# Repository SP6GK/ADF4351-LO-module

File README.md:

# High Quality RF Local Oscillator Module (ADF4351)

## Overview

This open-source PCB module is designed as a **drop in solution** for any project that requires a **high quality RF continuous wave signal** with at least **16 dBm output power**.  

I present more details on my website: [www.sp6gk.com](https://www.sp6gk.com/).

The design emphasizes:

- Output power (16–20 dBm depending on frequency)
- Low phase noise
- Minimal harmonics
- Easy integration into custom designs

Originally developed for the **Presto HF to QO-100 transverter project**, this module can be used in a wide variety of RF applications.

---

## Features & Specifications

| Parameter | Value |
|-----------|-------|
| **Optimal Frequency Range** | 400 MHz – 800 MHz (tunable for other ranges) or 1.5-2.1 GHz |
| **Output Power** | 20 dBm (50 Ω load) within optimal range |
| **Power Across Wide Range** | >17 dBm from 100 MHz to 2.4 GHz |
| **Phase Noise @ 400 MHz CW** | -89 dBc/Hz @ 100 Hz offset<br>-97 dBc/Hz @ 10 kHz offset |
| **Reference** | onboard 48 MHz 0.5 ppm VCTCXO + 12-bit DAC digital tuning (or external reference) |
| **Filtering** | Two selectable low-pass filters |
| **PLL Chipset** | Fractional-N PLL (Analog Devices ADF4351) |
| **Dimensions** | 85 × 57 mm |
| **Supply Voltage** | 3.6 V recommended (5.5 V absolute maximum) for logic, 5.3 V for PA stage (5.5 V absolute maximum) |
| **Current Consumption** | < 250 mA (can be reduced by disabling output) |
| **Calibration Storage** | On-board EEPROM |
| **Interface** | SPI (programming PLL) + 3.3 V input pins for switching filters, PA enable etc... |

---

## Applications

- Test and Measurement Equipment
- VHF/UHF Communication Systems
- Amateur Radio
- Backhaul network

---

## Current revisions:
- 400 to 800 MHz rev 01a (tested and presented in the measurements)
- 400 to 800 MHz rev 01b (adds triplexer before amplifier to minimize reflections)
- 1.5-2.1 GHz rev 01a (tuned for higher frequency, includes triplexer and microstrip LPF)

## Performance Measurements

Testing was performed using a **Keysight CXA Spectrum Analyzer (N9000B)** with the **phase noise measurement** option.

**100 MHz**  

**400 MHz**  

**1.2 GHz**  

---

### Harmonics & Output Spectra

**100 MHz CW (50 MHz span)**  

**400 MHz CW (10 MHz span)**  

---
Module was tested with STM32F407 discovery board, using driver written by [KB3GTN](https://github.com/kb3gtn/STM32_ADF4351).

---
### What's next?

I intended to use this module for driving a passive RF mixer, however since then I have learned that those work better with square wave LO with lower amplitude.

Currently I am working on revision of this board with LMX2572LP.
I have found this IC to be easier to program while offering better performance especially in terms of spurious emissions.

---

## Repository Contents
- **/ECAD** (Kicad Project, simulations)
- **/Fabrication** (Gerbers)
- **/Verification** (Measurements)
- **/Documents** (BOM)
- **/Photos** (photos of assembled PCB)

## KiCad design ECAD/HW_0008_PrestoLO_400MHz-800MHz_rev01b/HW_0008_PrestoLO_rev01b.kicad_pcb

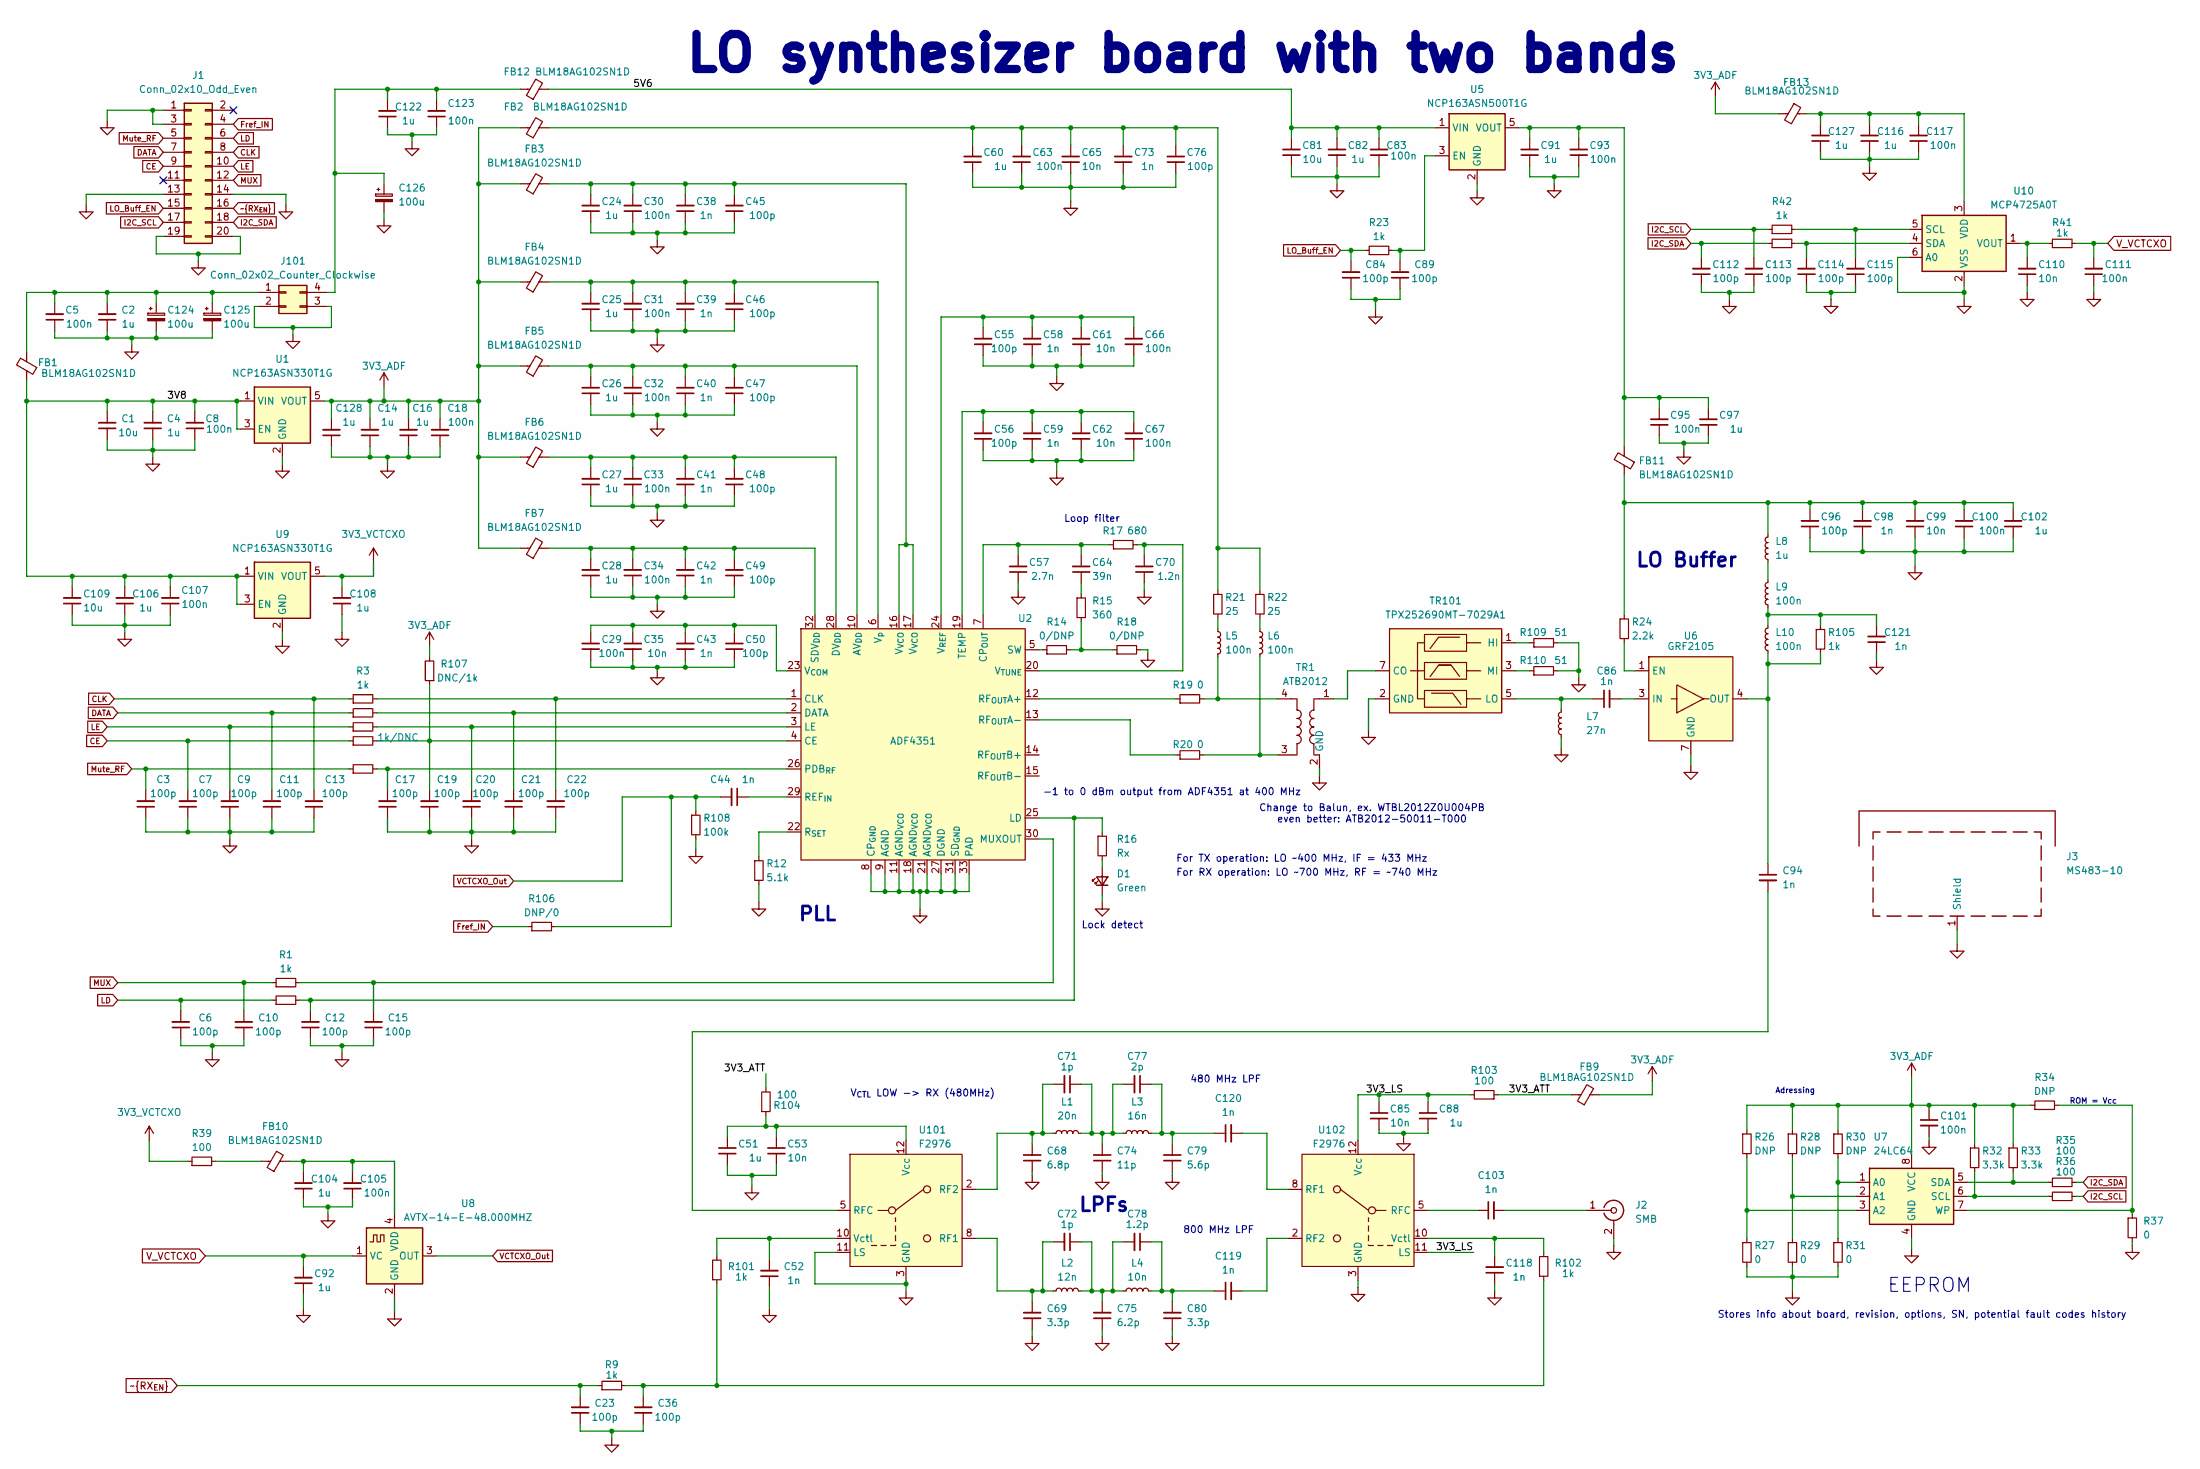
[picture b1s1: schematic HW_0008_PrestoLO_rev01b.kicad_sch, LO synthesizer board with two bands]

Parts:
C1, C81, C109: 10u; LED_0805_2012Metric
C2, C82, C91, C97, C122: 1u; C_0805_2012Metric_Pad1.18x1.45mm_HandSolder
C3, C6, C7, C9, C10, C11, C12, C13, C15, C17, C19, C20, C21, C22, C23, C36, C45, C46, C47, C48, C49, C50, C55, C56, C76, C84, C89, C96, C112, C113, C114, C115: 100p; C_0603_1608Metric_Pad1.08x0.95mm_HandSolder
C4, C14, C16, C24, C25, C26, C27, C28, C51, C60, C88, C92, C102, C104, C106, C108, C116, C127, C128: 1u; C_0603_1608Metric_Pad1.08x0.95mm_HandSolder
C5, C8, C18, C29, C30, C31, C32, C33, C34, C63, C66, C67, C83, C93, C95, C100, C101, C105, C107, C111, C117: 100n; C_0603_1608Metric_Pad1.08x0.95mm_HandSolder
C35, C61, C62, C65, C99, C110: 10n; C_0603_1608Metric_Pad1.08x0.95mm_HandSolder
C38, C39, C40, C41, C42, C43, C44, C58, C59, C73, C86, C94, C98, C103, C119, C120, C121: 1n; C_0603_1608Metric_Pad1.08x0.95mm_HandSolder
C52, C118: 1n; C_0402_1005Metric_Pad0.74x0.62mm_HandSolder
C53, C85: 10n; C_0402_1005Metric_Pad0.74x0.62mm_HandSolder
C57: 2.7n; C_0603_1608Metric_Pad1.08x0.95mm_HandSolder
C64: 39n; C_0603_1608Metric_Pad1.08x0.95mm_HandSolder
C68: 6.8p; C_0603_1608Metric
C69, C80: 3.3p; C_0603_1608Metric
C70: 1.2n; C_0603_1608Metric_Pad1.08x0.95mm_HandSolder
C71, C72: 1p; C_0603_1608Metric
C74: 11p; C_0603_1608Metric
C75: 6.2p; C_0603_1608Metric
C77: 2p; C_0603_1608Metric
C78: 1.2p; C_0603_1608Metric
C79: 5.6p; C_0603_1608Metric
C123: 100n; C_0805_2012Metric_Pad1.18x1.45mm_HandSolder
C124, C125, C126: 100u; CP_Elec_6.3x5.8
D1: Green; D_0805_2012Metric_Pad1.15x1.40mm_HandSolder
FB1: BLM18AG102SN1D; L_0805_2012Metric_Pad1.15x1.40mm_HandSolder
FB2, FB3, FB4, FB5, FB6, FB7, FB9, FB10, FB11, FB13: BLM18AG102SN1D; L_0603_1608Metric_Pad1.05x0.95mm_HandSolder
FB12: BLM18AG102SN1D; L_0805_2012Metric_Pad1.05x1.20mm_HandSolder
J1: Conn_02x10_Odd_Even; PinHeader_2x10_P2.54mm_Vertical
J2: SMB; SMB_Jack_Vertical
J3: MS483-10; MS4830-10
J101: Conn_02x02_Counter_Clockwise; PinHeader_2x02_P2.54mm_Vertical
L1: 20n; L_0603_1608Metric
L2: 12n; L_0603_1608Metric
L3: 16n; L_0603_1608Metric
L4: 10n; L_0603_1608Metric
L5, L6: 100n; L_0805_2012Metric_Pad1.15x1.40mm_HandSolder
L7: 27n; L_0805_2012Metric_Pad1.05x1.20mm_HandSolder
L8: 1u; L_0805_2012Metric_Pad1.05x1.20mm_HandSolder
L9: 100n; L_0805_2012Metric_Pad1.05x1.20mm_HandSolder
L10: 100n; L_0603_1608Metric_Pad1.05x0.95mm_HandSolder
R1, R2, R3, R4, R5, R7, R9, R23, R41, R42, R43, R105: 1k; R_0603_1608Metric_Pad0.98x0.95mm_HandSolder
R6: 1k/DNC; R_0603_1608Metric_Pad0.98x0.95mm_HandSolder
R12: 5.1k; R_0603_1608Metric_Pad0.98x0.95mm_HandSolder
R14, R18: 0/DNP; R_0603_1608Metric_Pad0.98x0.95mm_HandSolder
R15: 360; R_0603_1608Metric_Pad0.98x0.95mm_HandSolder
R16: Rx; R_0603_1608Metric_Pad0.98x0.95mm_HandSolder
R17: 680; R_0603_1608Metric_Pad0.98x0.95mm_HandSolder
R19, R20, R37: 0; R_0603_1608Metric_Pad0.98x0.95mm_HandSolder
R21, R22: 25; R_0603_1608Metric_Pad0.98x0.95mm_HandSolder
R24: 2.2k; R_0603_1608Metric_Pad0.98x0.95mm_HandSolder
R26, R28, R30: DNP; R_0805_2012Metric_Pad1.20x1.40mm_HandSolder
R27, R29, R31: 0; R_0805_2012Metric_Pad1.20x1.40mm_HandSolder
R32, R33: 3.3k; R_0603_1608Metric_Pad0.98x0.95mm_HandSolder
R34: DNP; R_0603_1608Metric_Pad0.98x0.95mm_HandSolder
R35, R36, R39: 100; R_0603_1608Metric_Pad0.98x0.95mm_HandSolder
R101, R102: 1k; R_0402_1005Metric_Pad0.72x0.64mm_HandSolder
R103, R104: 100; R_0402_1005Metric_Pad0.72x0.64mm_HandSolder
R106: DNP/0; R_0603_1608Metric_Pad0.98x0.95mm_HandSolder
R107: DNC/1k; R_0603_1608Metric_Pad0.98x0.95mm_HandSolder
R108: 100k; R_0603_1608Metric_Pad0.98x0.95mm_HandSolder
R109, R110: 51; R_0603_1608Metric_Pad0.98x0.95mm_HandSolder
TR1: ATB2012
TR101: TPX252690MT-7029A1; TPX252690MT-7029A
U1, U9: NCP163ASN330T1G; SOT-23-5
U2: ADF4351; LFCSP-32-1EP_5x5mm_P0.5mm_EP3.5x3.5mm_ThermalVias
U5: NCP163ASN500T1G; SOT-23-5
U6: GRF2105; DFN-6-1EP_2x2mm_P0.5mm_EP0.6x1.37mm
U7: 24LC64; SOIC-8_3.9x4.9mm_P1.27mm
U8: AVTX-14-E-48.000MHZ; AbracomAVTX_14
U10: MCP4725A0T; SOT-23-6
U101, U102: F2976

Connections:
3V3_ADF: C14.2, C16.2, C18.2, C101.1, C128.2, FB2.1, FB3.1, FB4.1, FB5.1, FB6.1, FB7.1, FB9.2, FB13.2, R26.1, R28.1, R30.1, R32.1, R33.1, R34.1, R107.2, U1.5 (VOUT), U7.8 (VCC)
3V3_VCTCXO: C108.2, R39.1, U9.5 (VOUT)
/3V3_ATT: FB9.1, R103.1, R104.2
/3V3_LS: C85.2, C88.2, R103.2, U102.11 (LS), U102.12 (Vcc)
/3V8: C1.2, C4.2, C8.2, C106.2, C107.2, C109.2, FB1.1, U1.1 (VIN), U1.3 (EN), U9.1 (VIN), U9.3 (EN)
/5V6: C81.2, C82.2, C83.2, FB12.2, U5.1 (VIN)
CE: C7.2, J1.9, R6.1
CLK: C13.2, J1.8, R3.1
DATA: C11.2, J1.7, R4.1
Fref_IN: J1.4, R106.1
GND: C1.1, C2.1, C3.1, C4.1, C5.1, C6.1, C7.1, C8.1, C9.1, C10.1, C11.1, C12.1, C13.1, C14.1, C15.1, C16.1, C17.1, C18.1, C19.1, C20.1, C21.1, C22.1, C23.1, C24.1, C25.1, C26.1, C27.1, C28.1, C29.1, C30.1, C31.1, C32.1, C33.1, C34.1, C35.1, C36.1, C38.1, C39.1, C40.1, C41.1, C42.1, C43.1, C45.1, C46.1, C47.1, C48.1, C49.1, C50.1, C51.1, C52.1, C53.1, C55.1, C56.1, C57.1, C58.1, C59.1, C60.1, C61.1, C62.1, C63.1, C65.1, C66.1, C67.1, C68.1, C69.1, C70.1, C73.1, C74.1, C75.1, C76.1, C79.1, C80.1, C81.1, C82.1, C83.1, C84.1, C85.1, C88.1, C89.1, C91.1, C92.1, C93.1, C95.1, C96.1, C97.1, C98.1, C99.1, C100.1, C101.2, C102.1, C104.1, C105.1, C106.1, C107.1, C108.1, C109.1, C110.1, C111.1, C112.1, C113.1, C114.1, C115.1, C116.1, C117.1, C118.1, C121.1, C122.1, C123.1, C124.2, C125.2, C126.2, C127.1, C128.1, D1.1 (K), J1.1, J1.3, J1.13, J1.14, J1.19, J1.20, J2.2 (Ext), J3.1 (Shield), J101.2, J101.3, L7.1, R12.2, R18.2, R27.2, R29.2, R31.2, R37.2, R108.2, R109.2, R110.2, TR1.2 (GND), TR101.2 (GND), TR101.4 (GND), TR101.6 (GND), TR101.8 (GND), TR101.9 (GND), U1.2 (GND), U2.8 (CP_{GND}), U2.9 (AGND), U2.11 (AGND_{VCO}), U2.18 (AGND_{VCO}), U2.21 (AGND_{VCO}), U2.27 (DGND), U2.31 (SD_{GND}), U2.33 (PAD), U5.2 (GND), U6.2 (GND), U6.5 (GND), U6.6 (GND), U6.7 (GND), U7.4 (GND), U8.2 (GND), U9.2 (GND), U10.2 (VSS), U10.6 (A0), U101.1 (GND), U101.3 (GND), U101.4 (GND), U101.6 (GND), U101.7 (GND), U101.9 (GND), U101.11 (LS), U101.EP (GND), U102.1 (GND), U102.3 (GND), U102.4 (GND), U102.6 (GND), U102.7 (GND), U102.9 (GND), U102.EP (GND)
I2C_SCL: C113.2, J1.17, R36.2, R42.1
I2C_SDA: C112.2, J1.18, R35.2, R43.1
LD: C6.2, J1.6, R2.1
LE: C9.2, J1.10, R5.1
LO_Buff_EN: C84.2, J1.15, R23.1
MUX: C10.2, J1.12, R1.1
Mute_RF: C3.2, J1.5, R7.1
unnamed: C24.2, C30.2, C38.2, C45.2, FB3.2, U2.16 (V_{VCO}), U2.17 (V_{VCO})
unnamed: C36.2, R9.2, R101.1, R102.1
unnamed: C60.2, C63.2, C65.2, C73.2, C76.2, FB2.2, R21.1, R22.1
unnamed: C64.1, R15.1
unnamed: C71.1, C74.2, C77.2, L1.2, L3.1
unnamed: C72.1, C75.2, C78.2, L2.2, L4.1
unnamed: C96.2, C98.2, C99.2, C100.2, C102.2, FB11.1, L8.2, R24.1
unnamed: C78.1, C80.2, C119.1, L4.2
unnamed: C77.1, C79.2, C120.1, L3.2
unnamed: C121.2, L9.1, L10.2, R105.1
unnamed: D1.2 (A), R16.2
unnamed: FB10.1, R39.2
unnamed: C103.2, J2.1 (In)
unnamed: C2.2, C5.2, C124.1, C125.1, FB1.2, J101.1
unnamed: C122.2, C123.2, C126.1, FB12.1, J101.4
unnamed: L5.1, R21.2
unnamed: L5.2, R19.2, TR1.4
unnamed: L6.1, R22.2
unnamed: L6.2, R20.2, TR1.3
unnamed: L8.1, L9.2
unnamed: R14.2, R15.2, R18.1
unnamed: TR1.1, TR101.7 (CO)
unnamed: R109.1, TR101.1 (HI)
unnamed: C86.1, L7.2, TR101.5 (LO)
unnamed: R110.1, TR101.3 (MI)
unnamed: C26.2, C32.2, C40.2, C47.2, FB5.2, U2.10 (AV_{DD})
unnamed: C19.2, R6.2, R107.1, U2.4 (CE)
unnamed: C22.2, R3.2, U2.1 (CLK)
unnamed: C57.2, C64.2, R17.1, U2.7 (CP_{OUT})
unnamed: C21.2, R4.2, U2.2 (DATA)
unnamed: C27.2, C33.2, C41.2, C48.2, FB6.2, U2.28 (DV_{DD})
unnamed: C12.2, R2.2, R16.1, U2.25 (LD)
unnamed: C20.2, R5.2, U2.3 (LE)
unnamed: C15.2, R1.2, U2.30 (MUXOUT)
unnamed: C17.2, R7.2, U2.26 (PDB_{RF})
unnamed: C44.1, U2.29 (REF_{IN})
unnamed: R19.1, U2.12 (RF_{OUT}A+)
unnamed: R20.1, U2.13 (RF_{OUT}A-)
unnamed: R12.1, U2.22 (R_{SET})
unnamed: C28.2, C34.2, C42.2, C49.2, FB7.2, U2.32 (SDV_{DD})
unnamed: R14.1, U2.5 (SW)
unnamed: C56.2, C59.2, C62.2, C67.2, U2.19 (TEMP)
unnamed: C29.2, C35.2, C43.2, C50.2, U2.23 (V_{COM})
unnamed: C55.2, C58.2, C61.2, C66.2, U2.24 (V_{REF})
unnamed: C70.2, R17.2, U2.20 (V_{TUNE})
unnamed: C25.2, C31.2, C39.2, C46.2, FB4.2, U2.6 (V_{p})
unnamed: C89.2, R23.2, U5.3 (EN)
unnamed: C91.2, C93.2, C95.2, C97.2, FB11.2, U5.5 (VOUT)
unnamed: R24.2, U6.1 (EN)
unnamed: C86.2, U6.3 (IN)
unnamed: C94.1, L10.1, R105.2, U6.4 (OUT)
unnamed: R30.2, R31.1, U7.1 (A0)
unnamed: R28.2, R29.1, U7.2 (A1)
unnamed: R26.2, R27.1, U7.3 (A2)
unnamed: R32.2, R36.1, U7.6 (SCL)
unnamed: R33.2, R35.1, U7.5 (SDA)
unnamed: R34.2, R37.1, U7.7 (WP)
unnamed: C104.2, C105.2, FB10.2, U8.4 (VDD)
unnamed: C115.2, R42.2, U10.5 (SCL)
unnamed: C114.2, R43.2, U10.4 (SDA)
unnamed: C116.2, C117.2, C127.2, FB13.1, U10.3 (VDD)
unnamed: C110.2, R41.1, U10.1 (VOUT)
unnamed: C69.2, C72.2, L2.1, U101.8 (RF1)
unnamed: C68.2, C71.2, L1.1, U101.2 (RF2)
unnamed: C94.2, U101.5 (RFC)
unnamed: C51.2, C53.2, R104.1, U101.12 (Vcc)
unnamed: C52.2, R101.2, U101.10 (Vctl)
unnamed: C120.2, U102.8 (RF1)
unnamed: C119.2, U102.2 (RF2)
unnamed: C103.1, U102.5 (RFC)
unnamed: C118.2, R102.2, U102.10 (Vctl)
VCTCXO_Out: C44.2, R106.2, R108.1, U8.3 (OUT)
V_VCTCXO: C92.2, C111.2, R41.2, U8.1 (VC)
~RX_{EN}: C23.2, J1.16, R9.1

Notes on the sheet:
EEPROM
LPFs
Adressing
-1 to 0 dBm output from ADF4351 at 400 MHz
800 MHz LPF
480 MHz LPF
Lock detect
PLL
For TX operation: LO ~400 MHz, IF = 433 MHz
LO Buffer
Loop filter
LO synthesizer board with two bands
For RX operation: LO ~700 MHz, RF = ~740 MHz
Stores info about board, revision, options, SN, potential fault codes history
Change to Balun, ex. WTBL2012Z0U004PB even better: ATB2012-50011-T000
ROM = Vcc
V_{CTL} LOW -> RX (480MHz)

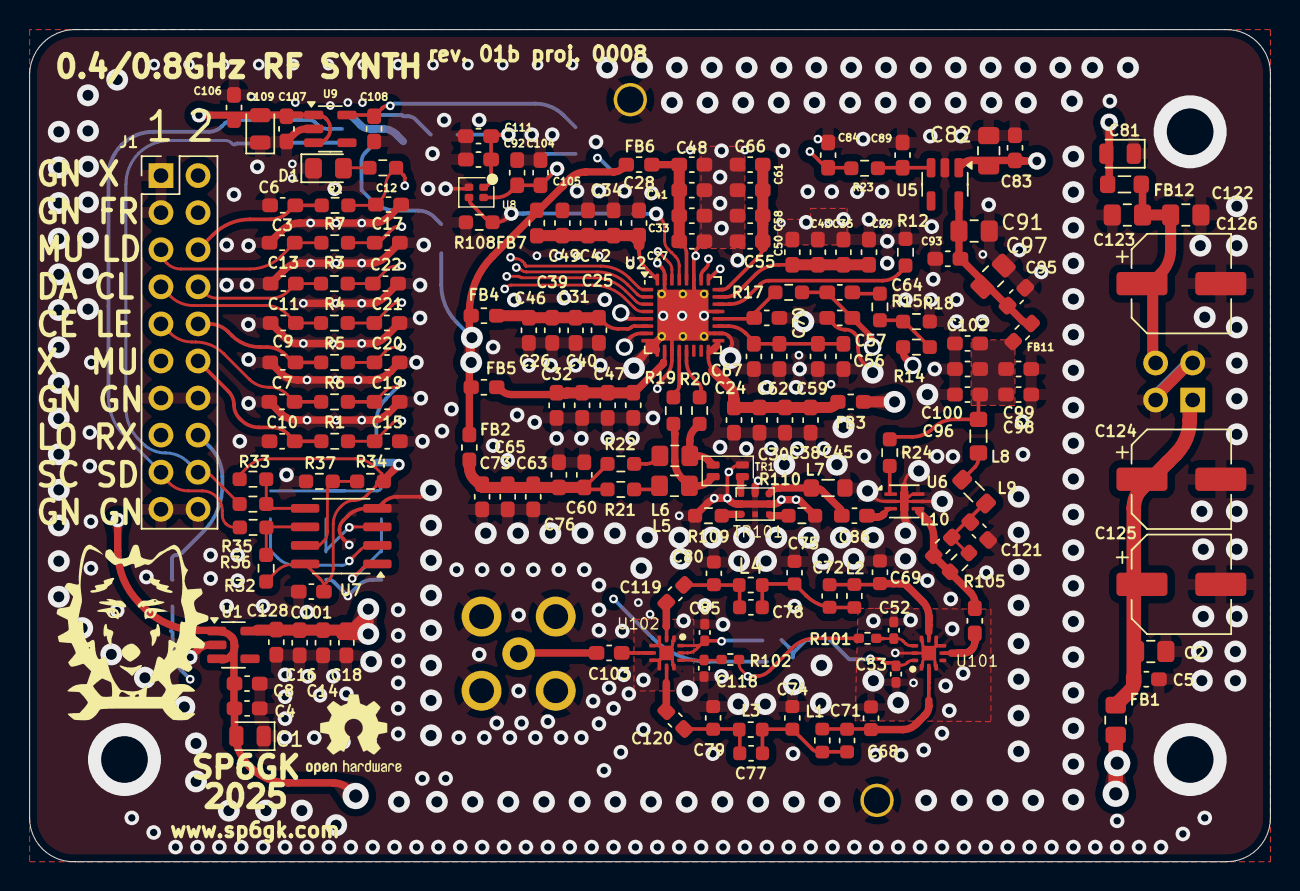
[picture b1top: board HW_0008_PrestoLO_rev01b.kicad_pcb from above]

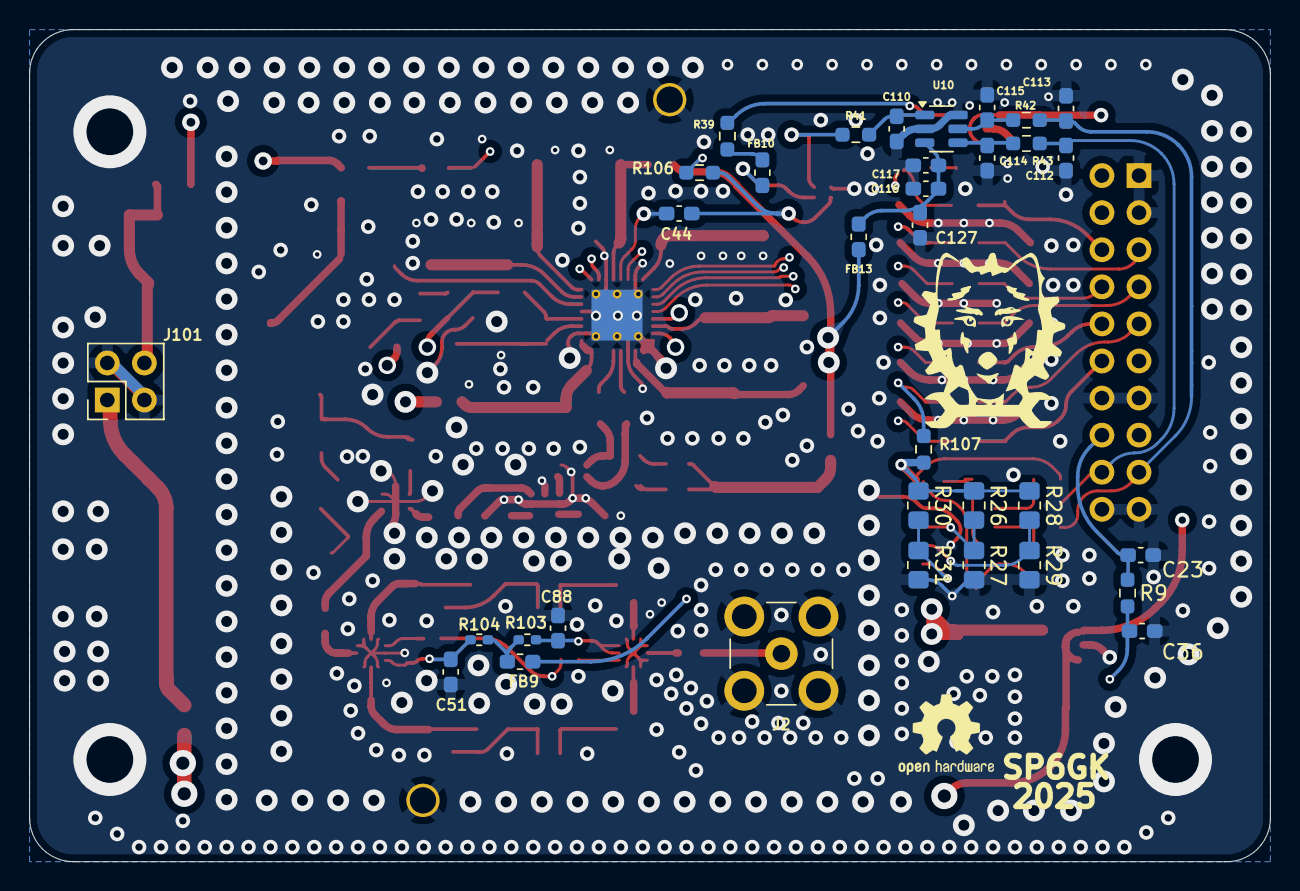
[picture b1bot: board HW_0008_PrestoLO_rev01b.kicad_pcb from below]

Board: 4 copper layers, 85.0 x 57.0 mm, 209 parts (34 on the bottom side), 92 nets.

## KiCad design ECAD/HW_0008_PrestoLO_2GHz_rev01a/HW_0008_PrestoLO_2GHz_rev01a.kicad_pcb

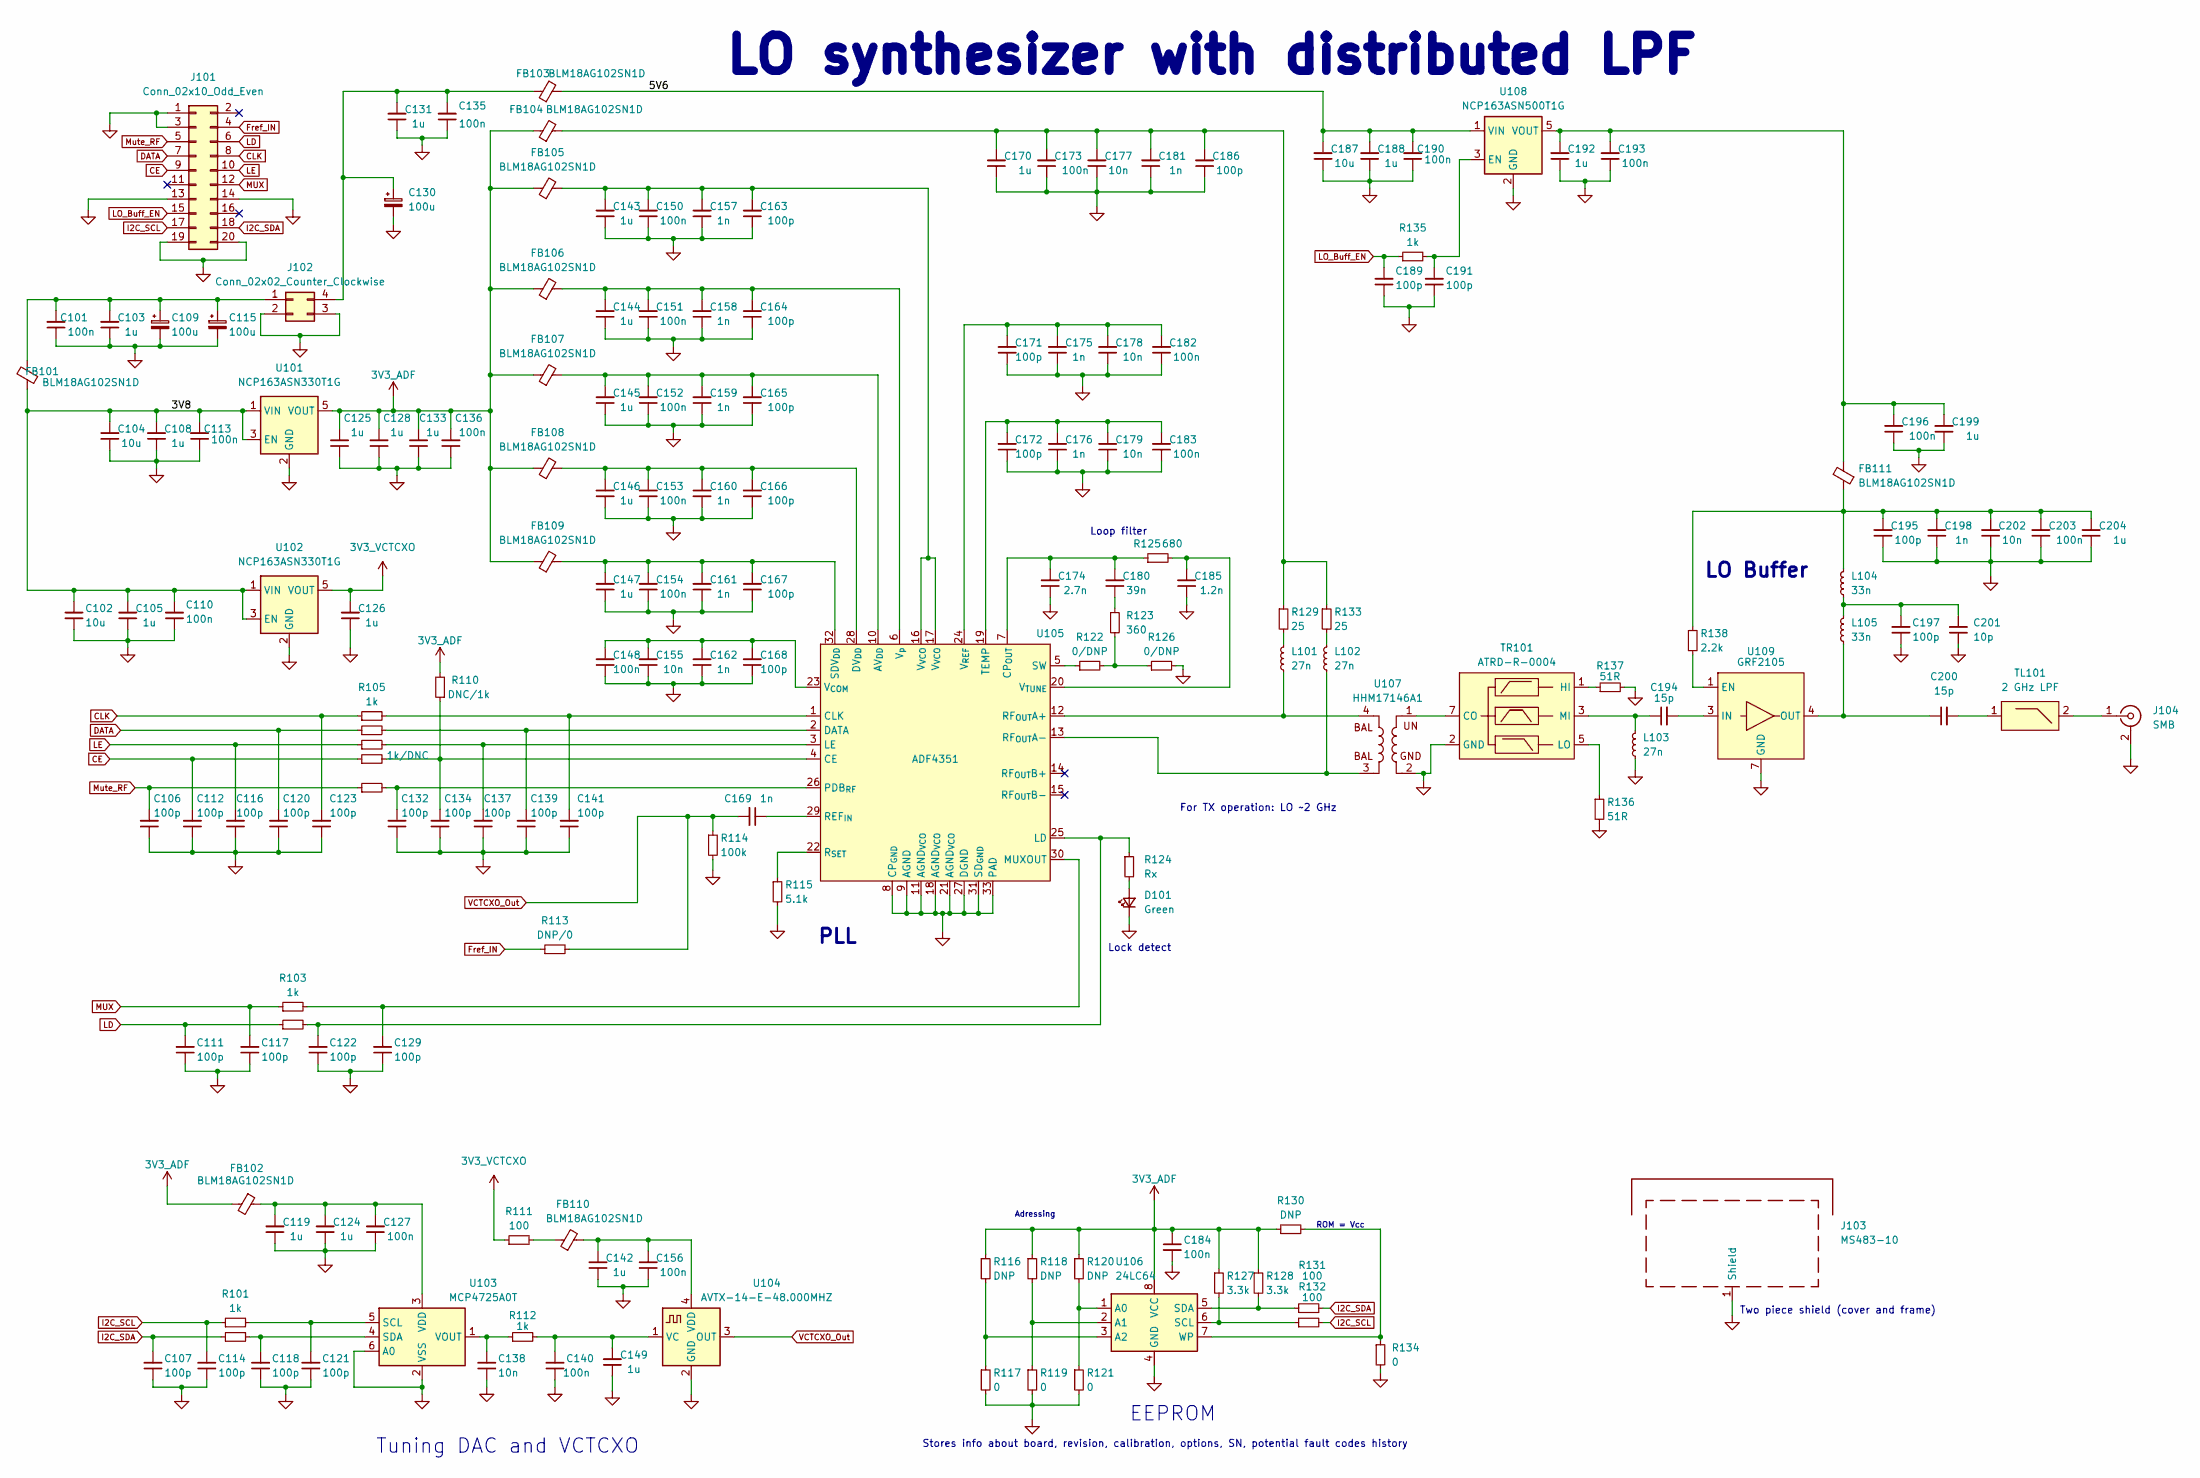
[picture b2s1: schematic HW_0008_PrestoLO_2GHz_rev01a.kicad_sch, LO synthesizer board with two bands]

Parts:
C101, C110, C113, C127, C136, C140, C148, C150, C151, C152, C153, C154, C156, C173, C182, C183, C184, C190, C193, C196, C203: 100n; C_0603_1608Metric_Pad1.08x0.95mm_HandSolder
C102, C104, C187: 10u; LED_0805_2012Metric
C103, C131, C188, C192, C199: 1u; C_0805_2012Metric_Pad1.18x1.45mm_HandSolder
C105, C108, C119, C124, C125, C126, C128, C133, C142, C143, C144, C145, C146, C147, C149, C170, C204: 1u; C_0603_1608Metric_Pad1.08x0.95mm_HandSolder
C106, C107, C111, C112, C114, C116, C117, C118, C120, C121, C122, C123, C129, C132, C134, C137, C139, C141, C163, C164, C165, C166, C167, C168, C171, C172, C186, C189, C191, C195, C197: 100p; C_0603_1608Metric_Pad1.08x0.95mm_HandSolder
C109, C115, C130: 100u; CP_Elec_6.3x5.8
C135: 100n; C_0805_2012Metric_Pad1.18x1.45mm_HandSolder
C138, C155, C177, C178, C179, C202: 10n; C_0603_1608Metric_Pad1.08x0.95mm_HandSolder
C157, C158, C159, C160, C161, C162, C169, C175, C176, C181, C198: 1n; C_0603_1608Metric_Pad1.08x0.95mm_HandSolder
C174: 2.7n; C_0603_1608Metric_Pad1.08x0.95mm_HandSolder
C180: 39n; C_0603_1608Metric_Pad1.08x0.95mm_HandSolder
C185: 1.2n; C_0603_1608Metric_Pad1.08x0.95mm_HandSolder
C194, C200: 15p; C_0603_1608Metric_Pad1.08x0.95mm_HandSolder
C201: 10p; C_0603_1608Metric_Pad1.08x0.95mm_HandSolder
D101: Green; D_0805_2012Metric_Pad1.15x1.40mm_HandSolder
FB101: BLM18AG102SN1D; L_0805_2012Metric_Pad1.15x1.40mm_HandSolder
FB102, FB104, FB105, FB106, FB107, FB108, FB109, FB110, FB111: BLM18AG102SN1D; L_0603_1608Metric_Pad1.05x0.95mm_HandSolder
FB103: BLM18AG102SN1D; L_0805_2012Metric_Pad1.05x1.20mm_HandSolder
J101: Conn_02x10_Odd_Even; PinHeader_2x10_P2.54mm_Vertical
J102: Conn_02x02_Counter_Clockwise; PinHeader_2x02_P2.54mm_Vertical
J103: MS483-10; MS4830-10
J104: SMB; SMB_Jack_Vertical
L101, L102, L103: 27n; L_0805_2012Metric_Pad1.05x1.20mm_HandSolder
L104, L105: 33n; L_0603_1608Metric_Pad1.05x0.95mm_HandSolder
R101, R102, R103, R104, R105, R106, R107, R109, R112, R135: 1k; R_0603_1608Metric_Pad0.98x0.95mm_HandSolder
R108: 1k/DNC; R_0603_1608Metric_Pad0.98x0.95mm_HandSolder
R110: DNC/1k; R_0603_1608Metric_Pad0.98x0.95mm_HandSolder
R111, R131, R132: 100; R_0603_1608Metric_Pad0.98x0.95mm_HandSolder
R113: DNP/0; R_0603_1608Metric_Pad0.98x0.95mm_HandSolder
R114: 100k; R_0603_1608Metric_Pad0.98x0.95mm_HandSolder
R115: 5.1k; R_0603_1608Metric_Pad0.98x0.95mm_HandSolder
R116, R118, R120: DNP; R_0805_2012Metric_Pad1.20x1.40mm_HandSolder
R117, R119, R121: 0; R_0805_2012Metric_Pad1.20x1.40mm_HandSolder
R122, R126: 0/DNP; R_0603_1608Metric_Pad0.98x0.95mm_HandSolder
R123: 360; R_0603_1608Metric_Pad0.98x0.95mm_HandSolder
R124: Rx; R_0603_1608Metric_Pad0.98x0.95mm_HandSolder
R125: 680; R_0603_1608Metric_Pad0.98x0.95mm_HandSolder
R127, R128: 3.3k; R_0603_1608Metric_Pad0.98x0.95mm_HandSolder
R129, R133: 25; R_0603_1608Metric_Pad0.98x0.95mm_HandSolder
R130: DNP; R_0603_1608Metric_Pad0.98x0.95mm_HandSolder
R134: 0; R_0603_1608Metric_Pad0.98x0.95mm_HandSolder
R136, R137: 51R; R_0402_1005Metric_Pad0.72x0.64mm_HandSolder
R138: 2.2k; R_0603_1608Metric_Pad0.98x0.95mm_HandSolder
TL101: 2 GHz LPF; Microstrip_2GHz_LPF
TR101: ATRD-R-0004; TPX252690MT-7029A
U101, U102: NCP163ASN330T1G; SOT-23-5
U103: MCP4725A0T; SOT-23-6
U104: AVTX-14-E-48.000MHZ; AbracomAVTX_14
U105: ADF4351; LFCSP-32-1EP_5x5mm_P0.5mm_EP3.5x3.5mm_ThermalVias
U106: 24LC64; SOIC-8_3.9x4.9mm_P1.27mm
U107: HHM17146A1
U108: NCP163ASN500T1G; SOT-23-5
U109: GRF2105; DFN-6-1EP_2x2mm_P0.5mm_EP0.6x1.37mm

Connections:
3V3_ADF: C125.2, C128.2, C133.2, C136.2, C184.1, FB102.2, FB104.1, FB105.1, FB106.1, FB107.1, FB108.1, FB109.1, R110.2, R116.1, R118.1, R120.1, R127.1, R128.1, R130.1, U101.5 (VOUT), U106.8 (VCC)
3V3_VCTCXO: C126.2, R111.1, U102.5 (VOUT)
/3V8: C102.2, C104.2, C105.2, C108.2, C110.2, C113.2, FB101.1, U101.1 (VIN), U101.3 (EN), U102.1 (VIN), U102.3 (EN)
/5V6: C187.2, C188.2, C190.2, FB103.2, U108.1 (VIN)
CE: C112.2, J101.9, R108.1
CLK: C123.2, J101.8, R105.1
DATA: C120.2, J101.7, R106.1
Fref_IN: J101.4, R113.1
GND: C101.1, C102.1, C103.1, C104.1, C105.1, C106.1, C107.1, C108.1, C109.2, C110.1, C111.1, C112.1, C113.1, C114.1, C115.2, C116.1, C117.1, C118.1, C119.1, C120.1, C121.1, C122.1, C123.1, C124.1, C125.1, C126.1, C127.1, C128.1, C129.1, C130.2, C131.1, C132.1, C133.1, C134.1, C135.1, C136.1, C137.1, C138.1, C139.1, C140.1, C141.1, C142.1, C143.1, C144.1, C145.1, C146.1, C147.1, C148.1, C149.1, C150.1, C151.1, C152.1, C153.1, C154.1, C155.1, C156.1, C157.1, C158.1, C159.1, C160.1, C161.1, C162.1, C163.1, C164.1, C165.1, C166.1, C167.1, C168.1, C170.1, C171.1, C172.1, C173.1, C174.1, C175.1, C176.1, C177.1, C178.1, C179.1, C181.1, C182.1, C183.1, C184.2, C185.1, C186.1, C187.1, C188.1, C189.1, C190.1, C191.1, C192.1, C193.1, C195.1, C196.1, C197.1, C198.1, C199.1, C201.1, C202.1, C203.1, C204.1, D101.1 (K), J101.1, J101.3, J101.13, J101.14, J101.19, J101.20, J102.2, J102.3, J103.1 (Shield), J104.2 (Ext), L103.1, R114.2, R115.2, R117.2, R119.2, R121.2, R126.2, R134.2, R136.2, R137.2, TR101.2 (GND), TR101.4 (GND), TR101.6 (GND), TR101.8 (GND), TR101.9 (GND), U101.2 (GND), U102.2 (GND), U103.2 (VSS), U103.6 (A0), U104.2 (GND), U105.8 (CP_{GND}), U105.9 (AGND), U105.11 (AGND_{VCO}), U105.18 (AGND_{VCO}), U105.21 (AGND_{VCO}), U105.27 (DGND), U105.31 (SD_{GND}), U105.33 (PAD), U106.4 (GND), U107.2, U107.5, U108.2 (GND), U109.2 (GND), U109.5 (GND), U109.6 (GND), U109.7 (GND)
I2C_SCL: C114.2, J101.17, R101.1, R132.2
I2C_SDA: C107.2, J101.18, R102.1, R131.2
LD: C111.2, J101.6, R104.1
LE: C116.2, J101.10, R107.1
LO_Buff_EN: C189.2, J101.15, R135.1
MUX: C117.2, J101.12, R103.1
Mute_RF: C106.2, J101.5, R109.1
unnamed: C143.2, C150.2, C157.2, C163.2, FB105.2, U105.16 (V_{VCO}), U105.17 (V_{VCO})
unnamed: C170.2, C173.2, C177.2, C181.2, C186.2, FB104.2, R129.1, R133.1
unnamed: C180.1, R123.1
unnamed: C195.2, C198.2, C202.2, C203.2, C204.2, FB111.1, L104.2, R138.1
unnamed: C197.2, C201.2, L104.1, L105.2
unnamed: C200.2, TL101.1
unnamed: D101.2 (A), R124.2
unnamed: FB110.1, R111.2
unnamed: C101.2, C103.2, C109.1, C115.1, FB101.2, J102.1
unnamed: C130.1, C131.2, C135.2, FB103.1, J102.4
unnamed: J104.1 (In), TL101.2
unnamed: L101.2, R129.2
unnamed: L102.2, R133.2
unnamed: R122.2, R123.2, R126.1
unnamed: TR101.7 (CO), U107.1
unnamed: R137.1, TR101.1 (HI)
unnamed: R136.1, TR101.5 (LO)
unnamed: C194.1, L103.2, TR101.3 (MI)
unnamed: C121.2, R101.2, U103.5 (SCL)
unnamed: C118.2, R102.2, U103.4 (SDA)
unnamed: C119.2, C124.2, C127.2, FB102.1, U103.3 (VDD)
unnamed: C138.2, R112.1, U103.1 (VOUT)
unnamed: C140.2, C149.2, R112.2, U104.1 (VC)
unnamed: C142.2, C156.2, FB110.2, U104.4 (VDD)
unnamed: C145.2, C152.2, C159.2, C165.2, FB107.2, U105.10 (AV_{DD})
unnamed: C134.2, R108.2, R110.1, U105.4 (CE)
unnamed: C141.2, R105.2, U105.1 (CLK)
unnamed: C174.2, C180.2, R125.1, U105.7 (CP_{OUT})
unnamed: C139.2, R106.2, U105.2 (DATA)
unnamed: C146.2, C153.2, C160.2, C166.2, FB108.2, U105.28 (DV_{DD})
unnamed: C122.2, R104.2, R124.1, U105.25 (LD)
unnamed: C137.2, R107.2, U105.3 (LE)
unnamed: C129.2, R103.2, U105.30 (MUXOUT)
unnamed: C132.2, R109.2, U105.26 (PDB_{RF})
unnamed: C169.1, U105.29 (REF_{IN})
unnamed: L101.1, U105.12 (RF_{OUT}A+), U107.4
unnamed: L102.1, U105.13 (RF_{OUT}A-), U107.3
unnamed: R115.1, U105.22 (R_{SET})
unnamed: C147.2, C154.2, C161.2, C167.2, FB109.2, U105.32 (SDV_{DD})
unnamed: R122.1, U105.5 (SW)
unnamed: C172.2, C176.2, C179.2, C183.2, U105.19 (TEMP)
unnamed: C148.2, C155.2, C162.2, C168.2, U105.23 (V_{COM})
unnamed: C171.2, C175.2, C178.2, C182.2, U105.24 (V_{REF})
unnamed: C185.2, R125.2, U105.20 (V_{TUNE})
unnamed: C144.2, C151.2, C158.2, C164.2, FB106.2, U105.6 (V_{p})
unnamed: R120.2, R121.1, U106.1 (A0)
unnamed: R118.2, R119.1, U106.2 (A1)
unnamed: R116.2, R117.1, U106.3 (A2)
unnamed: R127.2, R132.1, U106.6 (SCL)
unnamed: R128.2, R131.1, U106.5 (SDA)
unnamed: R130.2, R134.1, U106.7 (WP)
unnamed: C191.2, R135.2, U108.3 (EN)
unnamed: C192.2, C193.2, C196.2, C199.2, FB111.2, U108.5 (VOUT)
unnamed: R138.2, U109.1 (EN)
unnamed: C194.2, U109.3 (IN)
unnamed: C200.1, L105.1, U109.4 (OUT)
VCTCXO_Out: C169.2, R113.2, R114.1, U104.3 (OUT)

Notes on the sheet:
EEPROM
Two piece shield (cover and frame)
Adressing
Tuning DAC and VCTCXO
Lock detect
PLL
For TX operation: LO ~2 GHz
LO Buffer
Loop filter
LO synthesizer with distributed LPF
Stores info about board, revision, calibration, options, SN, potential fault codes history
ROM = Vcc

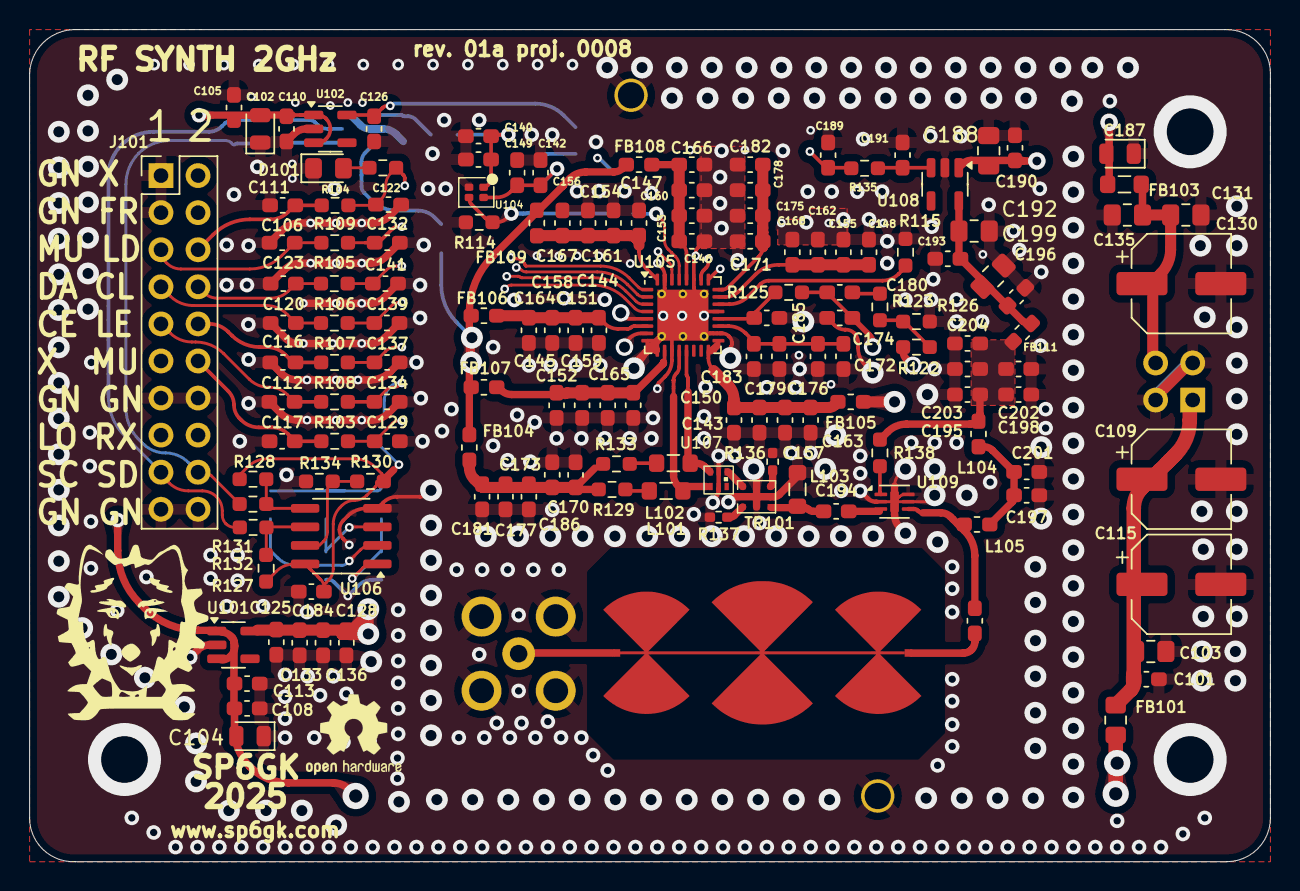
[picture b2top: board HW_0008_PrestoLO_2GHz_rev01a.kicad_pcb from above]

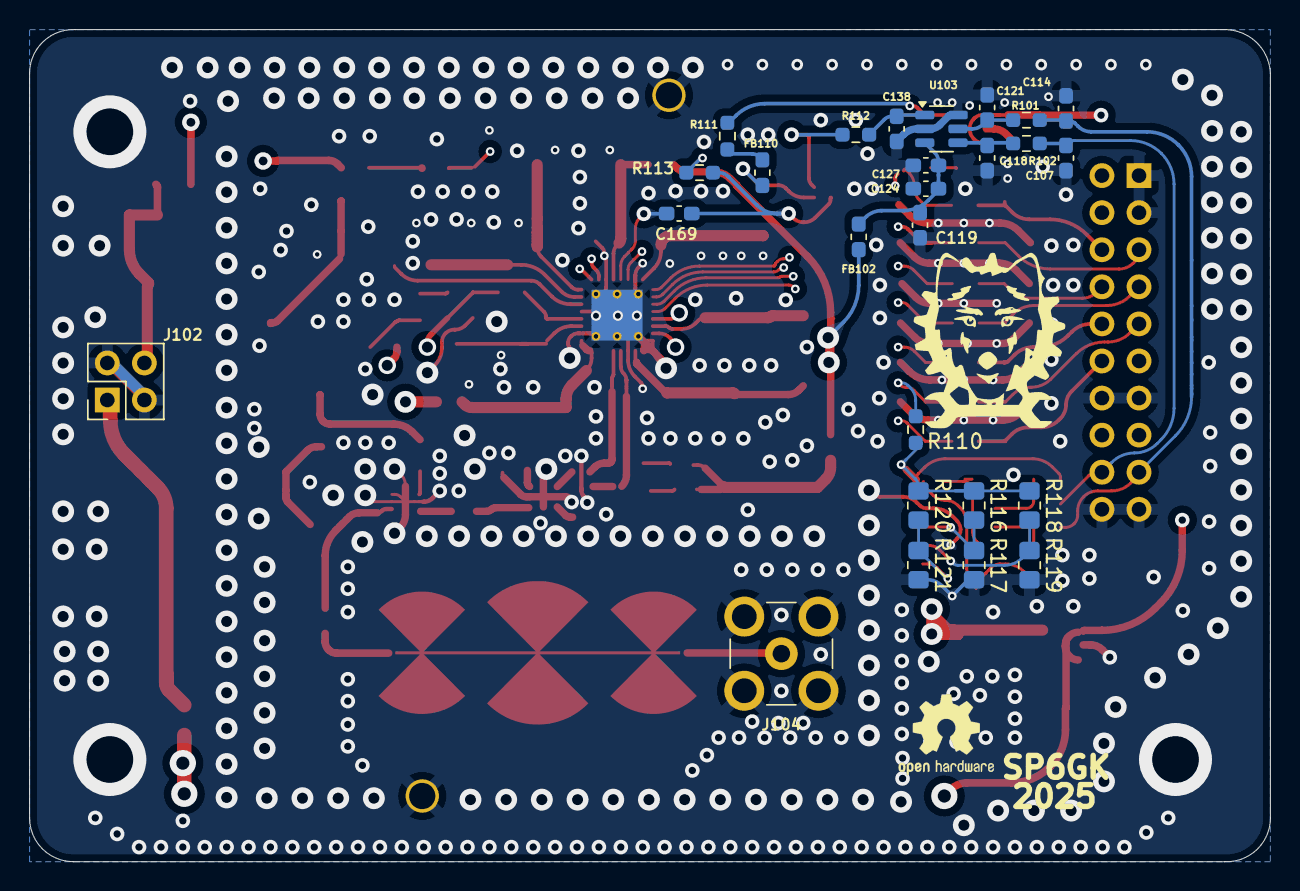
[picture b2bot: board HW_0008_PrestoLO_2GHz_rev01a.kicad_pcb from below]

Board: 4 copper layers, 85.0 x 57.0 mm, 174 parts (26 on the bottom side), 73 nets.

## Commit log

2026-02-08 Added triplexer (rev 01b) and 1.5-2.1 GHz variant
